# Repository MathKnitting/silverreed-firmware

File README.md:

# [Silverreed Firmware](./README.md)

<!-- Table of Contents -->

- [Installation](#installation)
- [Usage](#usage)
- [License](#license)

## Installation

This project leverages:
- PlatformIO for Arduino project management
- uv for Python dependency management
- taskipy for task automation

### Prerequisites

- Python 3.12 or higher
- [uv](https://docs.astral.sh/uv/) - Fast Python package installer

### Setup

1. Clone the repo
   ```shell
   git clone https://github.com/Knitall/silverreed-firmware.git
   cd silverreed-firmware
   ```

2. Install uv (if not already installed)
   ```shell
   curl -LsSf https://astral.sh/uv/install.sh | sh
   ```

3. Install dependencies
   ```shell
   uv sync --all-groups
   ```

4. Initialize the project
   ```shell
   uv run task init
   ```

## Usage

### Common Commands

```shell
# Build the firmware
uv run task build

# Build for specific environment
uv run task build -e uno
uv run task build -e unodebug    # With debug flags
uv run task build -e uno_r4_wifi # For Arduino UNO R4

# Upload to microcontroller
uv run task upload
uv run task upload -e uno

# Run tests
uv run task test
uv run task test -e simavr       # Run on AVR simulator
uv run task test -e native       # Run on native platform

# Run linter
uv run task lint

# Open serial monitor
uv run task monitor

# Documentation
uv run task docs-serve            # Serve locally with hot-reload
uv run task docs-build            # Build static site
uv run task docs-deploy           # Deploy to GitHub Pages

# Clean build artifacts
uv run task clean

# See all available tasks
uv run task --list
```

### Available Environments

- `uno` - Arduino UNO (default)
- `unodebug` - Arduino UNO with debug flags
- `uno_r4_wifi` - Arduino UNO R4 WiFi
- `simavr` - AVR simulator for testing
- `native` - Native platform for desktop tests

## License

Distributed under the MIT License. See [LICENSE](./LICENSE) for more information.

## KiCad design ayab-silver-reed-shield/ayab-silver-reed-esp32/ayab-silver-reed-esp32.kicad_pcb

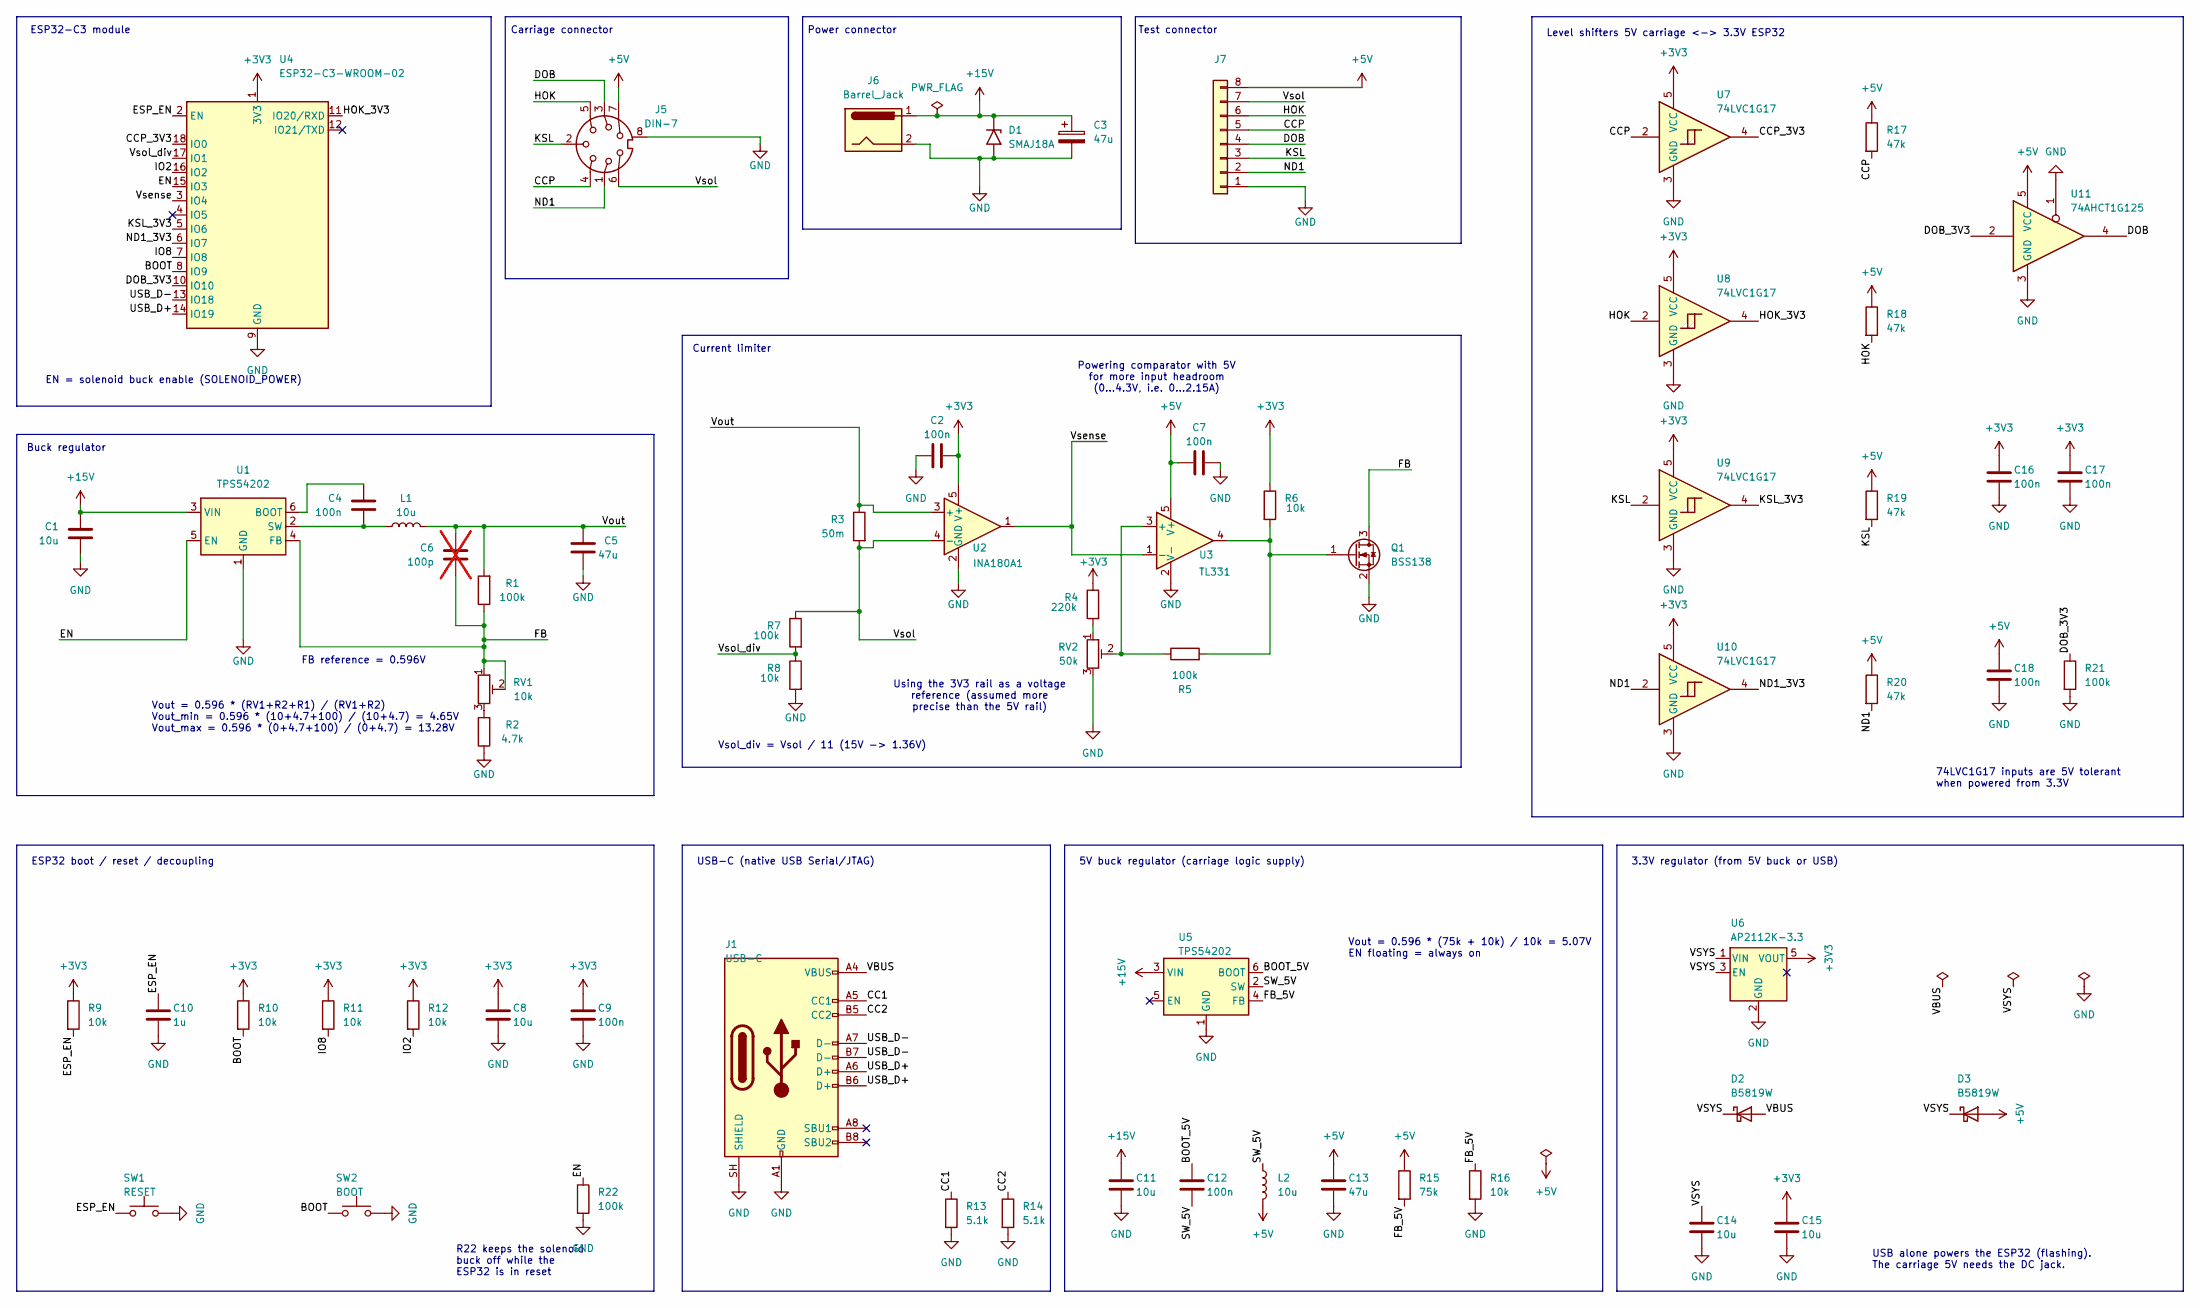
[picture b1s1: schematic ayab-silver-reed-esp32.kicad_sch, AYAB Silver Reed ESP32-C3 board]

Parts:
C1, C8, C11, C14, C15: 10u; C_0805_2012Metric; LCSC C15850
C2, C7, C9, C16, C17, C18: 100n; C_0603_1608Metric; LCSC C14663
C3: 47u; CP_Elec_5x5.9; LCSC C4747958
C4, C12: 100n; C_0805_2012Metric; LCSC C49678
C5, C13: 47u; C_1210_3225Metric; LCSC C7432791
C6: 100p; C_0603_1608Metric; LCSC C14858; not fitted
C10: 1u; C_0603_1608Metric; LCSC C15849
D1: SMAJ18A; D_SMA; LCSC C908771
D2, D3: B5819W; D_SOD-123; LCSC C8598
J1: USB-C; USB_C_Receptacle_HRO_TYPE-C-31-M-12; LCSC C165948
J5: DIN-7; DIN-704-M10; LCSC C20611695
J6: Barrel_Jack; BarrelJack_Horizontal; LCSC C720557
J7: Conn_01x08; PinSocket_1x08_P2.54mm_Vertical
L1, L2: 10u; L_Changjiang_FXL0518; LCSC C475910
Q1: BSS138; SOT-23; LCSC C7420339
R1, R5, R7, R21, R22: 100k; R_0603_1608Metric; LCSC C25803
R2: 4.7k; R_0603_1608Metric; LCSC C23162
R3: 50m; R_1206_3216Metric_Pad1.30x1.75mm_HandSolder; LCSC C5159739
R4: 220k; R_0603_1608Metric; LCSC C22961
R6, R8, R9, R10, R11, R12, R16: 10k; R_0603_1608Metric; LCSC C25804
R13, R14: 5.1k; R_0603_1608Metric; LCSC C23186
R15: 75k; R_0603_1608Metric; LCSC C23242
R17, R18, R19, R20: 47k; R_0603_1608Metric; LCSC C25819
RV1: 10k; Potentiometer_Bourns_TC33X_Vertical; LCSC C719176
RV2: 50k; Potentiometer_Bourns_TC33X_Vertical; LCSC C913246
SW1: RESET; SW_SPST_TL3342; LCSC C318884
SW2: BOOT; SW_SPST_TL3342; LCSC C318884
U1, U5: TPS54202; SOT-23-6; LCSC C191884
U2: INA180A1; SOT-23-5; LCSC C122228
U3: TL331; SOT-23-5; LCSC C3658524
U4: ESP32-C3-WROOM-02; LCSC C2934560
U6: AP2112K-3.3; SOT-23-5; LCSC C51118
U7, U8, U9, U10: 74LVC1G17; SOT-23-5; LCSC C7836
U11: 74AHCT1G125; SOT-23-5; LCSC C7484

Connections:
+3V3: C2.2, C8.1, C9.1, C15.1, C16.1, C17.1, R4.1, R6.1, R9.1, R10.1, R11.1, R12.1, U2.5 (V+), U4.1 (3V3), U6.5 (VOUT), U7.5 (VCC), U8.5 (VCC), U9.5 (VCC), U10.5 (VCC)
+5V: C7.1, C13.1, C18.1, D3.2 (A), J5.7, J7.8, L2.2, R15.1, R17.1, R18.1, R19.1, R20.1, U3.5 (V+), U11.5 (VCC)
+15V: C1.1, C3.1, C11.1, D1.1 (A1), J6.1, U1.3 (VIN), U5.3 (VIN)
/BOOT: R10.2, SW2.1, U4.8 (IO9)
/BOOT_5V: C12.1, U5.6 (BOOT)
/CC1: J1.A5 (CC1), R13.1
/CC2: J1.B5 (CC2), R14.1
/CCP: J5.4, J7.5, R17.2, U7.2
/CCP_3V3: U4.18 (IO0), U7.4
/DOB: J5.3, J7.4, U11.4
/DOB_3V3: R21.1, U4.10 (IO10), U11.2
/EN: R22.1, U1.5 (EN), U4.15 (IO3)
/ESP_EN: C10.1, R9.2, SW1.1, U4.2 (EN)
/FB: C6.2, Q1.3 (D), R1.1, RV1.1, RV1.2, U1.4 (FB)
/FB_5V: R15.2, R16.1, U5.4 (FB)
/HOK: J5.5, J7.6, R18.2, U8.2
/HOK_3V3: U4.11 (IO20/RXD), U8.4
/IO2: R12.2, U4.16 (IO2)
/IO8: R11.2, U4.7 (IO8)
/KSL: J5.2, J7.3, R19.2, U9.2
/KSL_3V3: U4.5 (IO6), U9.4
/ND1: J5.1, J7.2, R20.2, U10.2
/ND1_3V3: U4.6 (IO7), U10.4
/SW_5V: C12.2, L2.1, U5.2 (SW)
/USB_D+: J1.A6 (D+), J1.B6 (D+), U4.14 (IO19)
/USB_D-: J1.A7 (D-), J1.B7 (D-), U4.13 (IO18)
/VBUS: D2.2 (A), J1.A4 (VBUS), J1.A9 (VBUS), J1.B4 (VBUS), J1.B9 (VBUS)
/VSYS: C14.1, D2.1 (K), D3.1 (K), U6.1 (VIN), U6.3 (EN)
/Vout: C5.1, C6.1, L1.2, R1.2, R3.1, U2.3 (+)
/Vsense: U2.1, U3.1 (-), U4.3 (IO4)
/Vsol: J5.6, J7.7, R3.2, R7.1, U2.4 (-)
/Vsol_div: R7.2, R8.1, U4.17 (IO1)
GND: C1.2, C2.1, C3.2, C5.2, C7.2, C8.2, C9.2, C10.2, C11.2, C13.2, C14.2, C15.2, C16.2, C17.2, C18.2, D1.2 (A2), J1.A1 (GND), J1.A12 (GND), J1.B1 (GND), J1.B12 (GND), J1.SH (SHIELD), J5.8 (GND_8), J6.2, J7.1, Q1.2 (S), R2.1, R8.2, R13.2, R14.2, R16.2, R21.2, R22.2, RV2.3, SW1.2, SW2.2, U1.1 (GND), U2.2 (GND), U3.2 (V-), U4.9 (GND), U4.19 (GND), U5.1 (GND), U6.2 (GND), U7.3 (GND), U8.3 (GND), U9.3 (GND), U10.3 (GND), U11.1, U11.3 (GND)
unnamed: Q1.1 (G), R5.2, R6.2, U3.4
unnamed: R2.2, RV1.3
unnamed: R4.2, RV2.1
unnamed: C4.1, U1.6 (BOOT)
unnamed: C4.2, L1.1, U1.2 (SW)
unnamed: R5.1, RV2.2, U3.3 (+)

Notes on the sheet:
Power connector
Vsol_div = Vsol / 11 (15V -> 1.36V)
Using the 3V3 rail as a voltage reference (assumed more precise than the 5V rail)
FB reference = 0.596V
Carriage connector
Current limiter
Vout = 0.596 * (RV1+R2+R1) / (RV1+R2) Vout_min = 0.596 * (10+4.7+100) / (10+4.7) = 4.65V Vout_max = 0.596 * (0+4.7+100) / (0+4.7) = 13.28V
Powering comparator with 5V for more input headroom (0…4.3V, i.e. 0…2.15A)
Buck regulator
ESP32-C3 module
Test connector
EN = solenoid buck enable (SOLENOID_POWER)
ESP32 boot / reset / decoupling
R22 keeps the solenoid buck off while the ESP32 is in reset
USB-C (native USB Serial/JTAG)
5V buck regulator (carriage logic supply)
Vout = 0.596 * (75k + 10k) / 10k = 5.07V EN floating = always on
3.3V regulator (from 5V buck or USB)
USB alone powers the ESP32 (flashing). The carriage 5V needs the DC jack.
Level shifters 5V carriage <-> 3.3V ESP32
74LVC1G17 inputs are 5V tolerant when powered from 3.3V

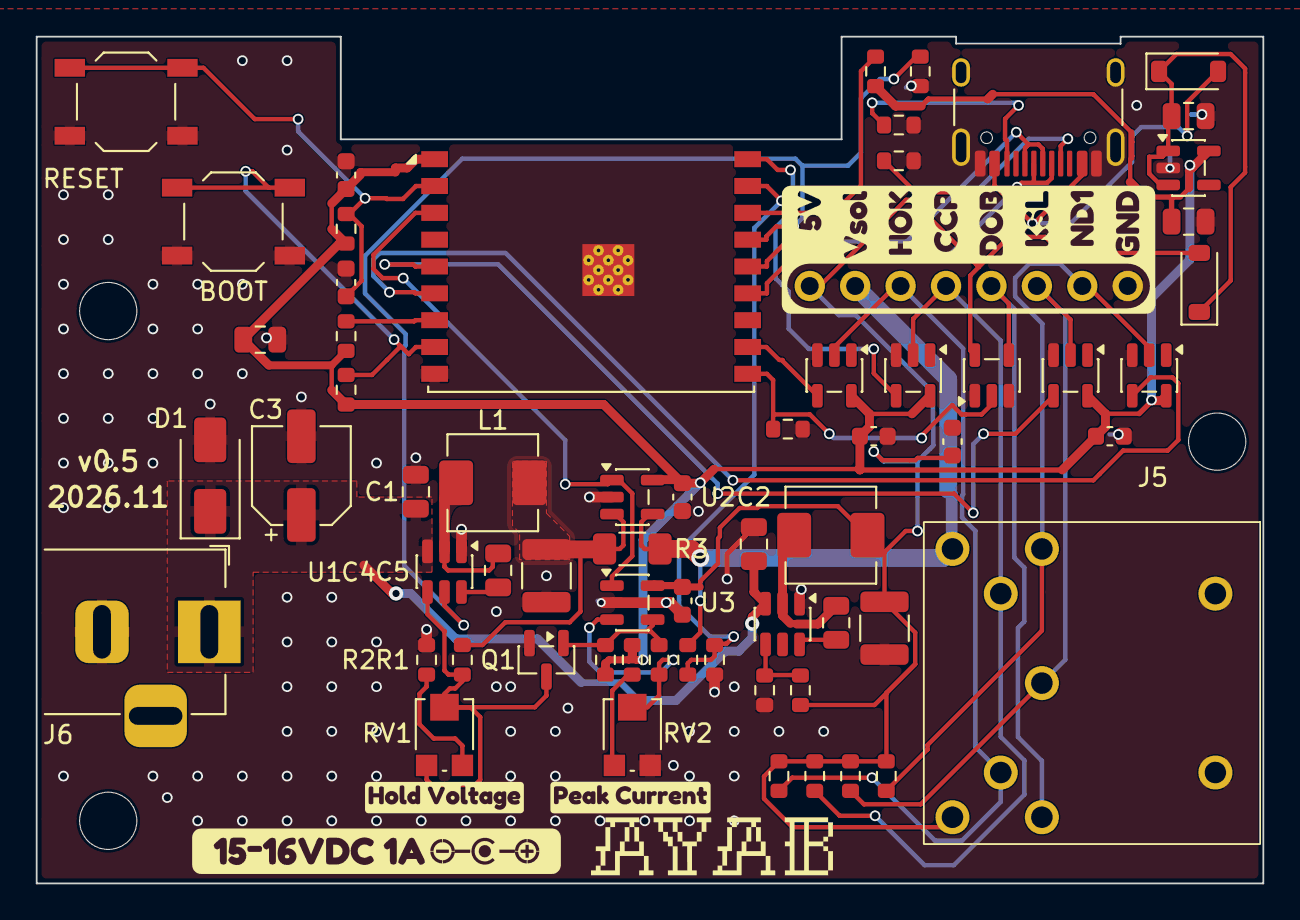
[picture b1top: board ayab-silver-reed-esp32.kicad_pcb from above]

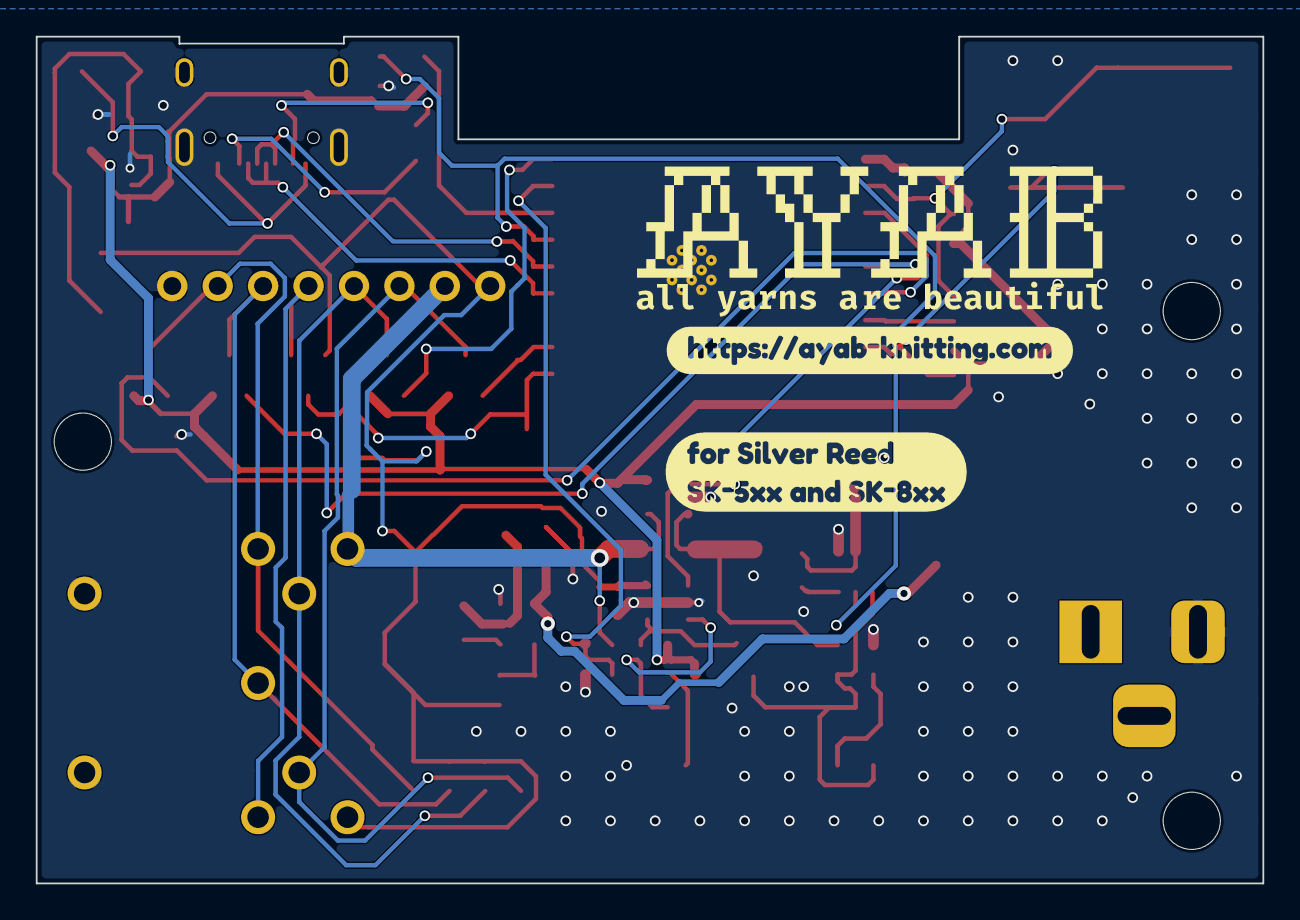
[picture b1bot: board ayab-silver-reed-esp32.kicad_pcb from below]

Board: 2 copper layers, 68.6 x 47.3 mm, 73 parts (2 on the bottom side), 39 nets.

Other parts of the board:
MH1, MH2, MH3: MountingHole_3.2mm
kobee-studio-6A8D70C3: G***; kobee-studio-6A8D70C3
kobee-studio-6A8D711F: G***; kobee-studio-6A8D711F
kobee-studio-6A8D7125: G***; kobee-studio-6A8D7125
kobee-studio-6A70D9B2: G***; kobee-studio-6A70D9B2
kobee-studio-6A70E057: G***; kobee-studio-6A70E057
kobee-studio-6A712065: G***; kobee-studio-6A712065

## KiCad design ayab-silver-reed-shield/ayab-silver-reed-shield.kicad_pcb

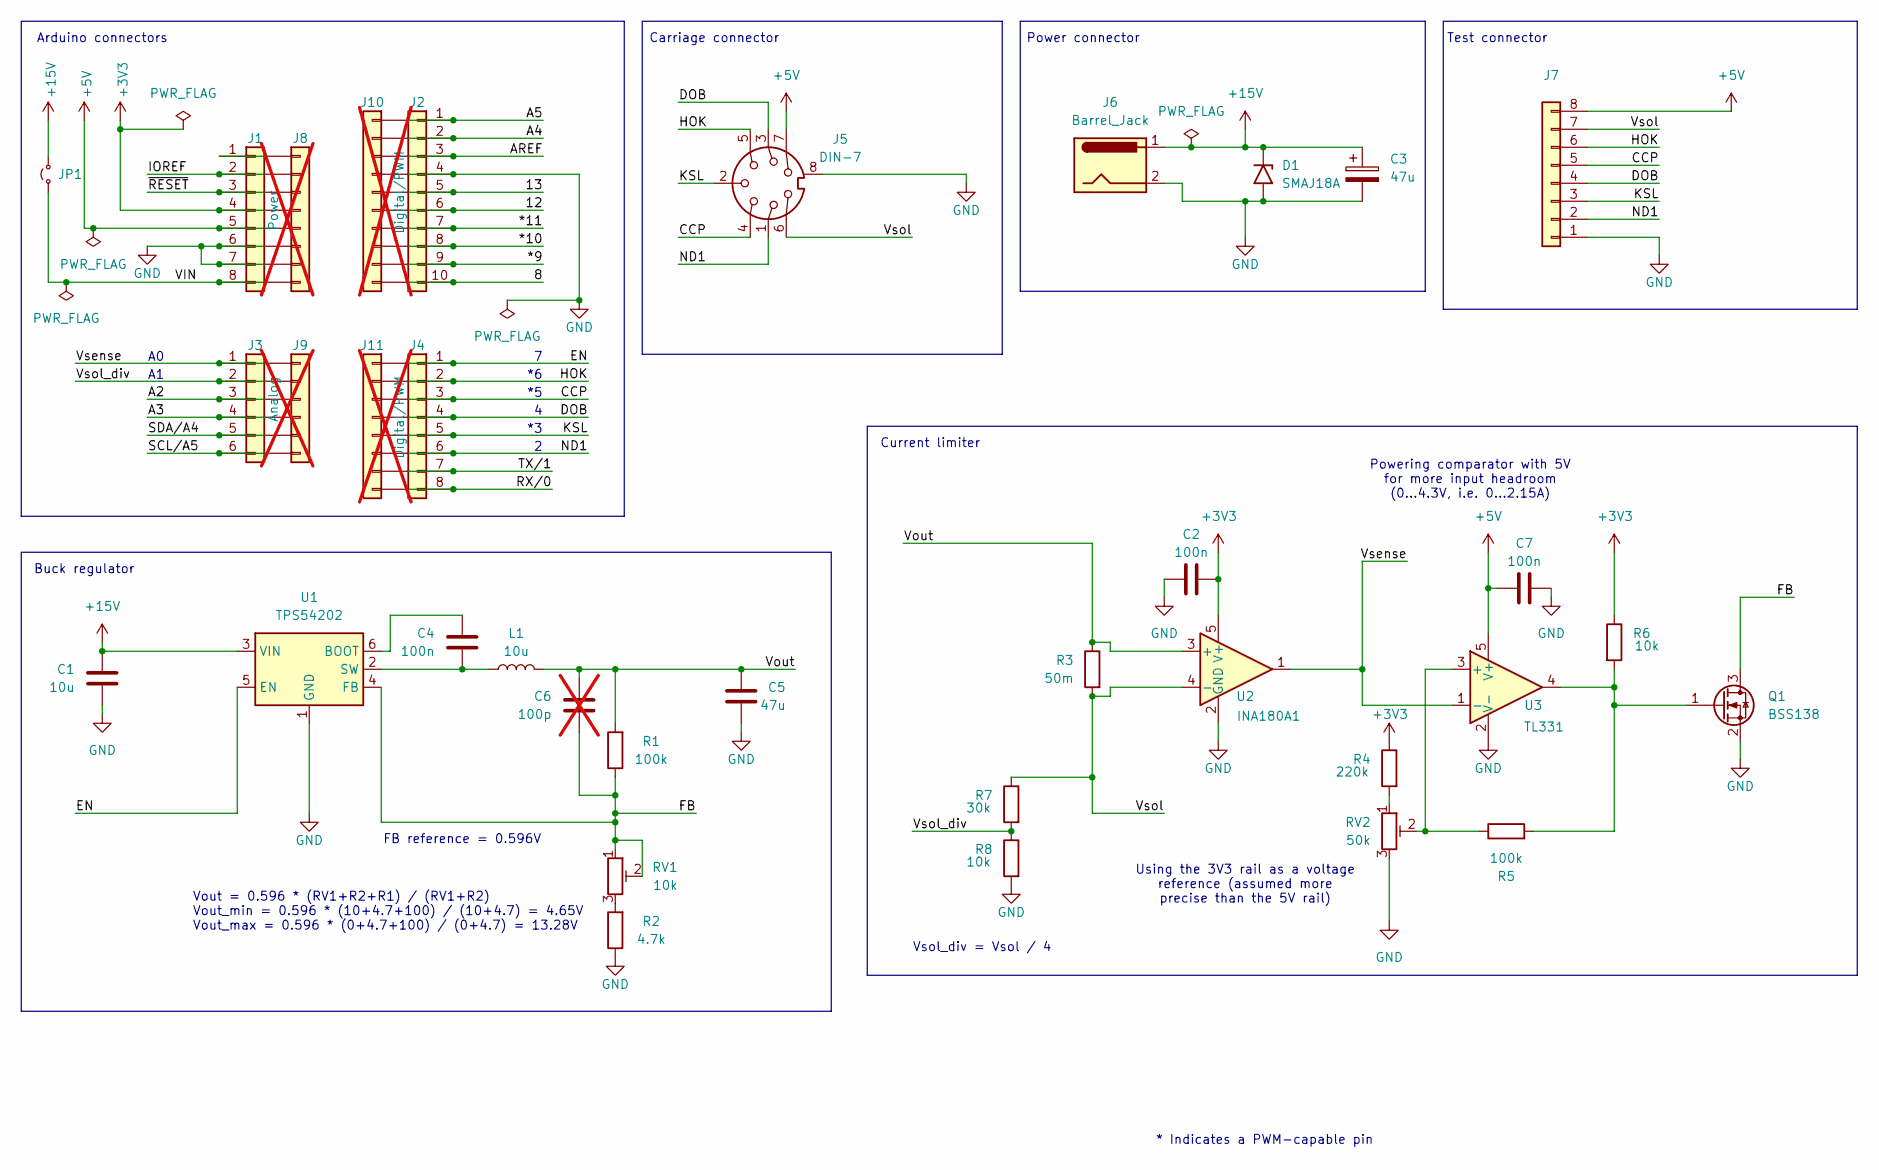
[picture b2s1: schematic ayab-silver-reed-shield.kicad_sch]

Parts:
C1: 10u; C_0805_2012Metric; LCSC C15850
C2, C7: 100n; C_0603_1608Metric; LCSC C14663
C3: 47u; CP_Elec_5x5.9; LCSC C4747958
C4: 100n; C_0805_2012Metric; LCSC C49678
C5: 47u; C_1210_3225Metric; LCSC C7432791
C6: 100p; C_0603_1608Metric; LCSC C14858; not fitted
D1: SMAJ18A; D_SMA; LCSC C908771
J1: Power; PinHeader_1x08_P2.54mm_Vertical
J2: Digital/PWM; PinHeader_1x10_P2.54mm_Vertical
J3: Analog; PinHeader_1x06_P2.54mm_Vertical
J4: Digital/PWM; PinHeader_1x08_P2.54mm_Vertical
J5: DIN-7; DIN-704-M10; LCSC C20611695
J6: Barrel_Jack; BarrelJack_Horizontal; LCSC C720557
J7: Conn_01x08; PinSocket_1x08_P2.54mm_Vertical
J8: Power; PinHeader_1x08_P2.54mm_Vertical; not fitted
J9: Analog; PinHeader_1x06_P2.54mm_Vertical; not fitted
J10: Digital/PWM; PinHeader_1x10_P2.54mm_Vertical; not fitted
J11: Digital/PWM; PinHeader_1x08_P2.54mm_Vertical; not fitted
JP1: Jumper_2_Small_Open; PinHeader_1x02_P2.54mm_Vertical
L1: 10u; L_Changjiang_FXL0518; LCSC C475910
Q1: BSS138; SOT-23; LCSC C7420339
R1, R5: 100k; R_0603_1608Metric; LCSC C25803
R2: 4.7k; R_0603_1608Metric; LCSC C23162
R3: 50m; R_1206_3216Metric_Pad1.30x1.75mm_HandSolder; LCSC C25334
R4: 220k; R_0603_1608Metric; LCSC C22961
R6, R8: 10k; R_0603_1608Metric; LCSC C25804
R7: 30k; R_0603_1608Metric; LCSC C22984
RV1: 10k; Potentiometer_Bourns_TC33X_Vertical; LCSC C719176
RV2: 50k; Potentiometer_Bourns_TC33X_Vertical; LCSC C913246
U1: TPS54202; SOT-23-6; LCSC C191884
U2: INA180A1; SOT-23-5; LCSC C122228
U3: TL331; SOT-23-5; LCSC C3658524

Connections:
+3V3: C2.2, J1.4, J8.4, R4.1, R6.1, U2.5 (V+)
+5V: C7.1, J1.5, J5.7, J7.8, J8.5, U3.5 (V+)
+15V: C1.1, C3.1, D1.1 (A1), J6.1, JP1.2 (B), U1.3 (VIN)
/8: J2.10, J10.10
/12: J2.6, J10.6
/13: J2.5, J10.5
/*9: J2.9, J10.9
/*10: J2.8, J10.8
/*11: J2.7, J10.7
/A2: J3.3, J9.3
/A3: J3.4, J9.4
/A4: J2.2, J10.2
/A5: J2.1, J10.1
/AREF: J2.3, J10.3
/CCP: J4.3, J5.4, J7.5, J11.3
/DOB: J4.4, J5.3, J7.4, J11.4
/EN: J4.1, J11.1, U1.5 (EN)
/FB: C6.2, Q1.3 (D), R1.1, RV1.1, RV1.2, U1.4 (FB)
/HOK: J4.2, J5.5, J7.6, J11.2
/IOREF: J1.2, J8.2
/KSL: J4.5, J5.2, J7.3, J11.5
/ND1: J4.6, J5.1, J7.2, J11.6
/RX/0: J4.8, J11.8
/SCL/A5: J3.6, J9.6
/SDA/A4: J3.5, J9.5
/TX/1: J4.7, J11.7
/VIN: J1.8, J8.8, JP1.1 (A)
/Vout: C5.1, C6.1, L1.2, R1.2, R3.1, U2.3 (+)
/Vsense: J3.1, J9.1, U2.1, U3.1 (-)
/Vsol: J5.6, J7.7, R3.2, R7.1, U2.4 (-)
/Vsol_div: J3.2, J9.2, R7.2, R8.1
/~RESET: J1.3, J8.3
GND: C1.2, C2.1, C3.2, C5.2, C7.2, D1.2 (A2), J1.6, J1.7, J2.4, J5.8 (GND_8), J6.2, J7.1, J8.6, J8.7, J10.4, Q1.2 (S), R2.1, R8.2, RV2.3, U1.1 (GND), U2.2 (GND), U3.2 (V-)
unnamed: J1.1, J8.1
unnamed: Q1.1 (G), R5.2, R6.2, U3.4
unnamed: R2.2, RV1.3
unnamed: R4.2, RV2.1
unnamed: C4.1, U1.6 (BOOT)
unnamed: C4.2, L1.1, U1.2 (SW)
unnamed: R5.1, RV2.2, U3.3 (+)

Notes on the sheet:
Power connector
Vsol_div = Vsol / 4
Using the 3V3 rail as a voltage reference (assumed more precise than the 5V rail)
FB reference = 0.596V
Carriage connector
Current limiter
Vout = 0.596 * (RV1+R2+R1) / (RV1+R2) Vout_min = 0.596 * (10+4.7+100) / (10+4.7) = 4.65V Vout_max = 0.596 * (0+4.7+100) / (0+4.7) = 13.28V
Powering comparator with 5V for more input headroom (0…4.3V, i.e. 0…2.15A)
Buck regulator
Arduino connectors
* Indicates a PWM-capable pin
Test connector

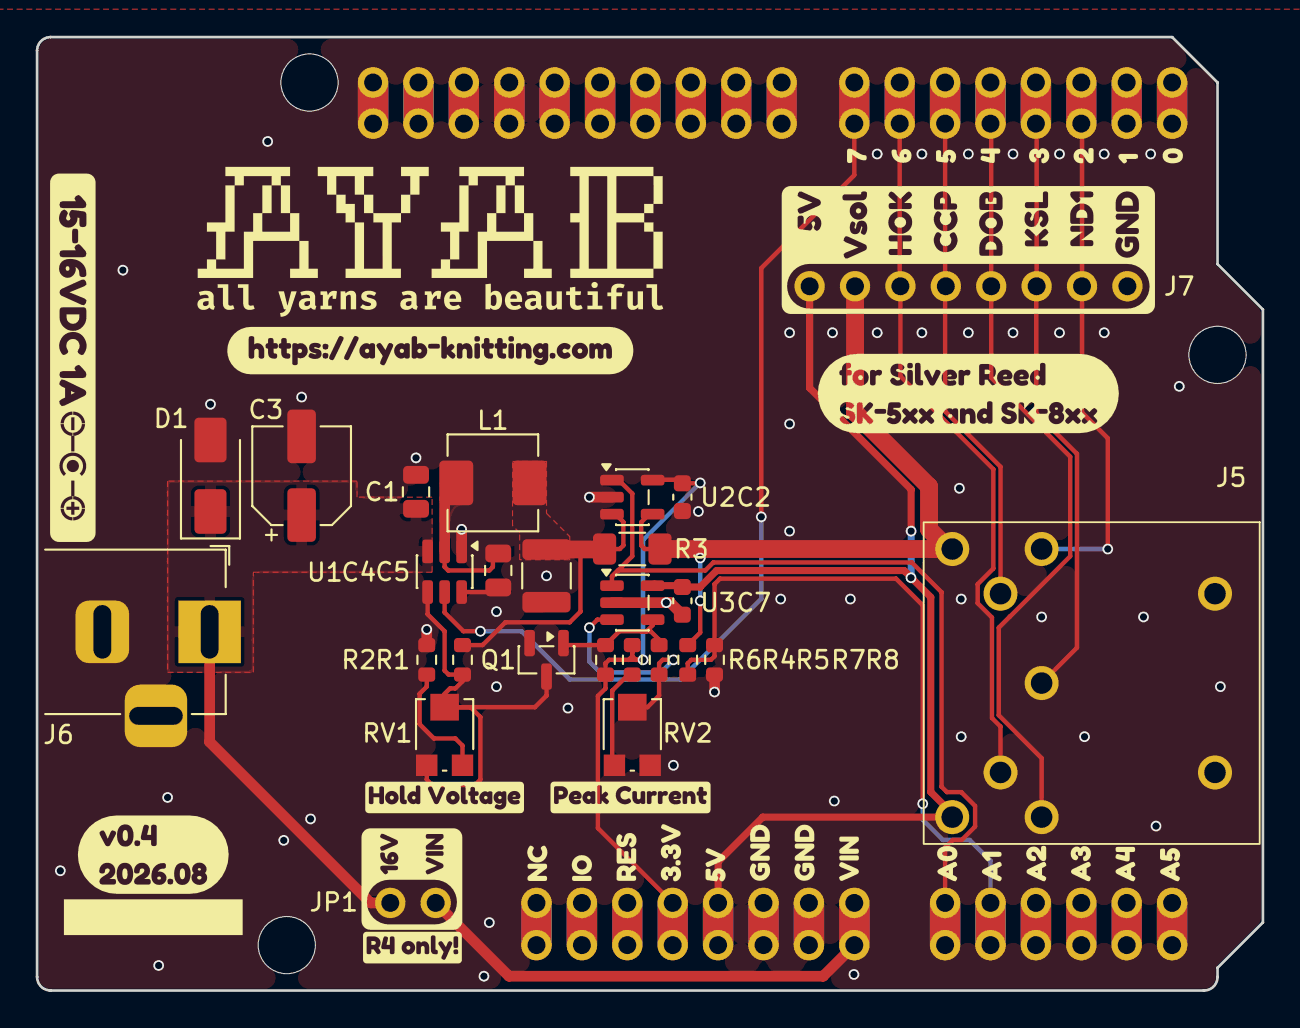
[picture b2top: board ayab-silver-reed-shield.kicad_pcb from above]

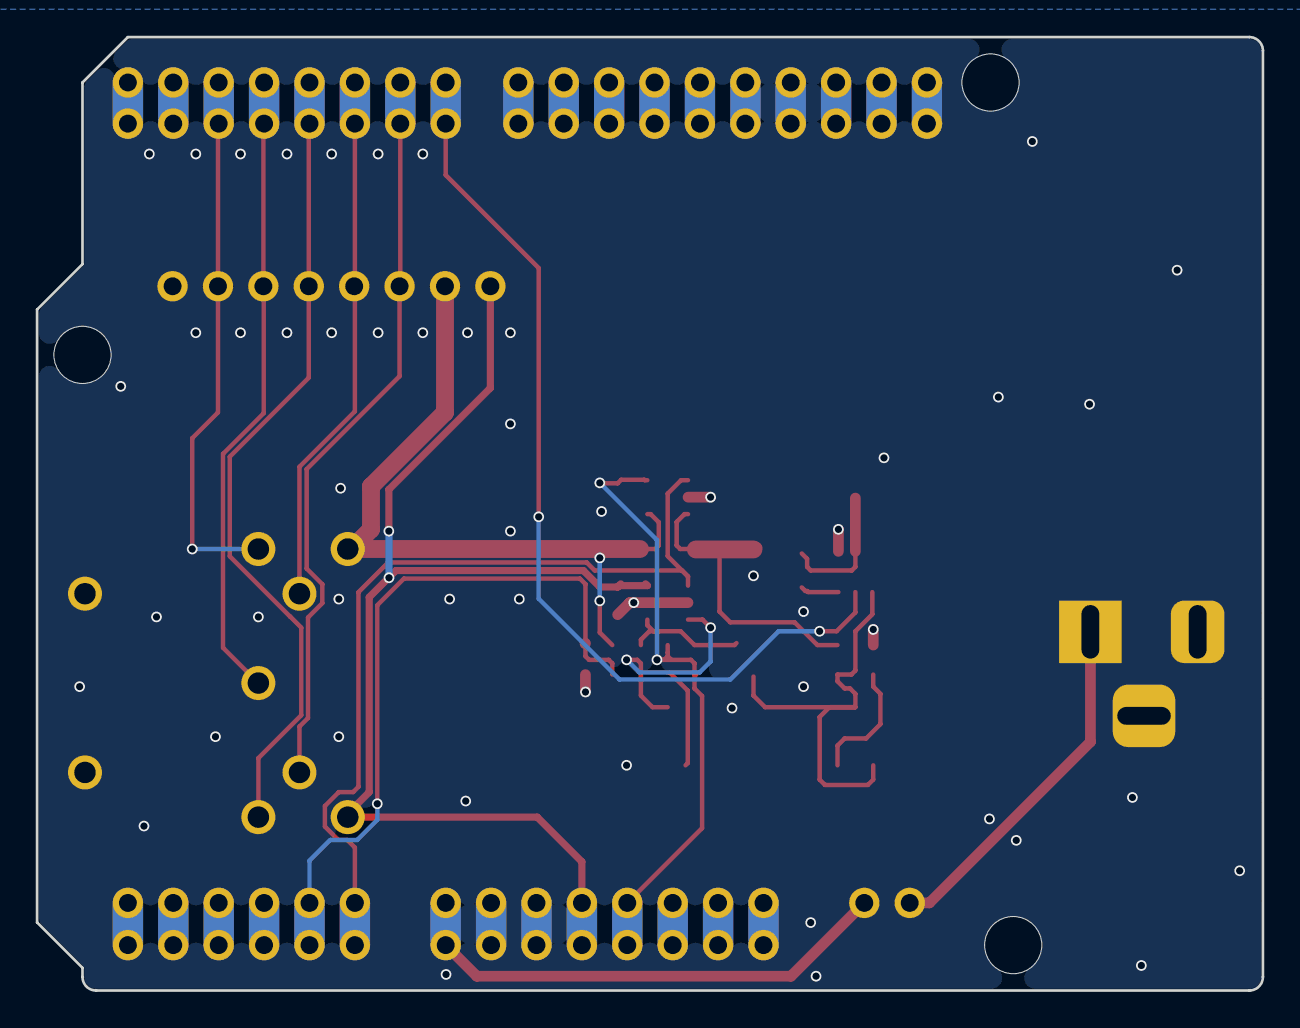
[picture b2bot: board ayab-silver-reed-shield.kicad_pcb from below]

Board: 2 copper layers, 68.6 x 53.3 mm, 50 parts (4 on the bottom side), 40 nets.

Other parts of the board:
MH1, MH2, MH3: MountingHole_3.2mm
kobee-studio-6A8D6F3B: G***; kobee-studio-6A8D6F3B
kobee-studio-6A8D6FDA: G***; kobee-studio-6A8D6FDA
kobee-studio-6A8D70C3: G***; kobee-studio-6A8D70C3
kobee-studio-6A8D711F: G***; kobee-studio-6A8D711F
kobee-studio-6A8D7125: G***; kobee-studio-6A8D7125
kobee-studio-6A70D9B2: G***; kobee-studio-6A70D9B2
kobee-studio-6A70E057: G***; kobee-studio-6A70E057
kobee-studio-6A7763EA: G***; kobee-studio-6A7763EA
kobee-studio-6A7763FF: G***; kobee-studio-6A7763FF
kobee-studio-6A77138D: G***; kobee-studio-6A77138D
kobee-studio-6A712065: G***; kobee-studio-6A712065
kobee-studio-6A776375: G***; kobee-studio-6A776375
kobee-studio-6A821817: G***; kobee-studio-6A821817

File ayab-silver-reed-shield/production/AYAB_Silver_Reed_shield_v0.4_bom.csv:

Designator,Footprint,Quantity,Value,LCSC Part #
C1,0805,1,10u,C15850
"C2, C7",0603,2,100n,C14663
C3,CP_Elec_5x5.9,1,47u,C4747958
C4,0805,1,100n,C49678
C5,1210,1,47u,C7432791
D1,D_SMA,1,SMAJ18A,C908771
J5,DIN-704-M10,1,DIN-7,C20611695
J6,BarrelJack_Horizontal,1,Barrel_Jack,C720557
L1,L_Changjiang_FXL0518,1,10u,C475910
Q1,SOT-23,1,BSS138,C7420339
"R1, R5",0603,2,100k,C25803
R2,0603,1,5k,C99782
R3,1206,1,50m,C25334
R4,0603,1,220k,C22961
"R6, R8",0603,2,10k,C2906982
R7,0603,1,30k,C22984
RV1,Potentiometer_Bourns_TC33X_Vertical,1,10k,C719176
RV2,Potentiometer_Bourns_TC33X_Vertical,1,50k,C913246
U1,SOT-23-6,1,TPS54202,C191884
U2,SOT-23-5,1,INA180A1,C122228
U3,SOT-23-5,1,TL331,C3658524

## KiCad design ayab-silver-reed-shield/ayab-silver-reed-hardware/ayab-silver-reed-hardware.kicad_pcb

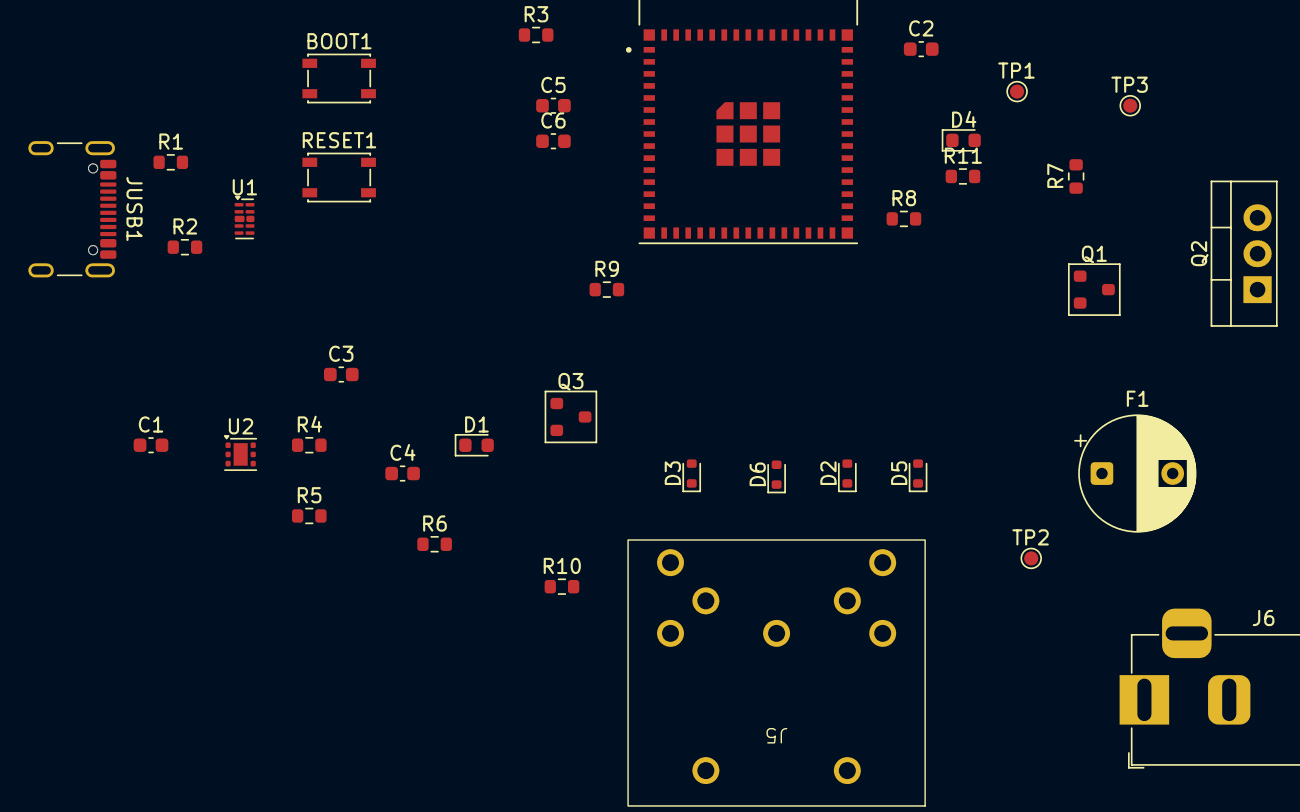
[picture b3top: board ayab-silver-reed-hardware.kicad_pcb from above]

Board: 2 copper layers, 38 parts (0 on the bottom side), 29 nets, no tracks yet.

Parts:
BOOT1: SW_SPST_PTS810
C1, C4, C6: 10uF; C_0603_1608Metric
C2, C3, C5: 0.1uF; C_0603_1608Metric
D1, D4: LED; LED_0603_1608Metric
D2, D3, D5, D6: 1N4148WT; D_SOD-523
F1: Polyfuse; CP_Radial_D8.0mm_P5.00mm
J5: DIN-7; DIN-704-M10
J6: Barrel_Jack; BarrelJack_Horizontal
JUSB1: USB_C_Receptacle_USB2.0_16P; USB_C_Receptacle_GCT_USB4105-xx-A_16P_TopMnt_Horizontal
Q1, Q3: MMBT2222A; SOT-23
Q2: Q_PMOS_GDS; TO-220-3_Vertical
R1, R2, R6: 5.1k; R_0603_1608Metric
R3, R4, R5, R7: 10k; R_0603_1608Metric
R8, R9, R10, R11: 1k; R_0603_1608Metric
RESET1: SW_SPST_PTS810
TP1: GND; TestPoint_Pad_D1.0mm
TP2: 16V; TestPoint_Pad_D1.0mm
TP3: 5V; TestPoint_Pad_D1.0mm
U1: D3V3XA4B10LP; Diodes_UDFN-10_1x2.5mm_P0.5mm
U2: TLV75801PDRV; WSON-6-1EP_2x2mm_P0.65mm_EP1x1.6mm
U3: ESP32-S3-MINI-1-N8; XCVR_ESP32-S3-MINI-1-N8

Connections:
/3V3: C4.2, C5.2, C6.2, R3.1, R4.1, R6.1, U2.1 (OUT), U3.3 (3V3)
/3vCCP: D2.2 (A), U3.19 (IO15)
/3vDOB: R9.2, U3.18 (IO14)
/3vHOK: D3.2 (A), U3.16 (IO12)
/3vKSL: D6.2 (A), U3.17 (IO13)
/3vND1: D5.2 (A), U3.20 (IO16)
/5VUSB: C1.2, J5.7, JUSB1.A4 (VBUS), JUSB1.A9 (VBUS), JUSB1.B4 (VBUS), JUSB1.B9 (VBUS), R10.1, TP3.1, U1.4, U2.4 (EN), U2.6 (IN)
/16VControlled: F1.1, J5.6, TP2.1
/16vIN: J6.1, Q2.3 (S), R7.2, R11.2
/CCP: D2.1 (K), J5.4
/DOB: J5.3, Q3.3 (C), R10.2
/ESP32_EN: C2.2, R3.2, U3.45 (EN)
/GPIO0: C3.2, U3.4 (IO0)
/HOK: D3.1 (K), J5.5
/KSL: D6.1 (K), J5.2
/ND1: D5.1 (K), J5.1
/SolenoidControl: R8.2, U3.21 (IO17)
/USB_N: JUSB1.A7 (D-), JUSB1.B7 (D-), U1.2, U3.23 (IO19)
/USB_P: JUSB1.A6 (D+), JUSB1.B6 (D+), U1.1, U3.24 (IO20)
GND: BOOT1.1, BOOT1.2, C1.1, C2.1, C3.1, C4.1, C5.1, C6.1, D1.1 (K), D4.1 (K), J5.8 (GND), J6.2, JUSB1.A1 (GND), JUSB1.A12 (GND), JUSB1.B1 (GND), JUSB1.B12 (GND), JUSB1.S1 (SHIELD), Q1.1 (E), Q3.1 (E), R1.2, R2.1, R5.2, RESET1.1, RESET1.2, TP1.1, U1.3 (VSS), U1.8 (VSS), U2.3 (GND), U2.7 (GND), U3.1 (GND), U3.2 (GND), U3.42 (GND), U3.43 (GND), U3.46 (GND), U3.47 (GND), U3.48 (GND), U3.49 (GND), U3.50 (GND), U3.51 (GND), U3.52 (GND), U3.53 (GND), U3.54 (GND), U3.55 (GND), U3.56 (GND), U3.57 (GND), U3.58 (GND), U3.59 (GND), U3.60 (GND), U3.61 (GND), U3.61_1 (GND), U3.61_2 (GND), U3.61_3 (GND), U3.61_4 (GND), U3.61_5 (GND), U3.61_6 (GND), U3.61_7 (GND), U3.61_8 (GND), U3.62 (GND), U3.63 (GND), U3.64 (GND), U3.65 (GND)
unnamed: D1.2 (A), R6.2
unnamed: D4.2 (A), R11.1
unnamed: JUSB1.A5 (CC1), R1.1
unnamed: JUSB1.B5 (CC2), R2.2
unnamed: Q1.2 (B), R8.1
unnamed: Q1.3 (C), Q2.1 (G), R7.1
unnamed: F1.2, Q2.2 (D)
unnamed: Q3.2 (B), R9.1
unnamed: R4.2, R5.1, U2.2 (FB)

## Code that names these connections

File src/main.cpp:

/**
 * Entry point of the Arduino.
 */
#include <Arduino.h>

#include "communication/ayab.h"
#include "config.h"
#include "debug.h"
#include "knitting.h"
#include "machine/carriage.h"

void setup() {
  /**
   * Setup run at the start of the Arduino.
   */
  // Set the pin modes for input pins.
  pinMode(PinsCorrespondance::ND1, INPUT_PULLUP);  // not used for now
  pinMode(PinsCorrespondance::KSL, INPUT_PULLUP);
  pinMode(PinsCorrespondance::DOB, OUTPUT);
  pinMode(PinsCorrespondance::CCP, INPUT_PULLUP);
  pinMode(PinsCorrespondance::HOK, INPUT_PULLUP);
  pinMode(PinsCorrespondance::SOLENOID_POWER, OUTPUT);

  // Initialize carriage output pins (DOB and SOLENOID_POWER) to safe state.
  // This handles DOB signal inversion automatically for platforms that need it.
  Carriage::secure_carriage();

  // Initialize the program singletons.
  Ayab.init();
  KnittingProcess.reset();

  // DEBUG
  DEBUG_START();
  DEBUG_PRINTLN("Init done");
}

void loop() {
  /**
   * Loop run continuously after the setup.
   */
  Ayab.update();
  KnittingProcess.knitting_loop();
}
